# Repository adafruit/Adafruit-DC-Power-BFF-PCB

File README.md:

## Adafruit DC Power BFF Add-On for QT Py PCB

<a href="http://www.adafruit.com/products/5882"><br/>
Click here to purchase one from the Adafruit shop</a>

PCB files for the Adafruit DC Power BFF Add-On for QT Py. 

Format is EagleCAD schematic and board layout
* https://www.adafruit.com/product/5882

### Description

We were recently working on a project where we really wanted to power a QT Py ESP32 from 12V - but the only power input on the board is basically USB 5V max. Never one to give up, we designed an add-on that will allow anyone to use a QT Py or Xiao dev board with up to 20V DC power!

In the center is an MPM3610 integrated buck converter, which will generate 5V from up to 20V input, with cool DC/DC technology so there's no heat-sink needed. The MPM3610 can give about 1 Amp output, which should be plenty even if you have LEDs, WiFi connectivity, displays or even a small motor or servo.

The board features both 3.5mm terminal block and 2.1mm DC jack inputs, protected with a Schottky diode. You can use either to power the board, but don't plug in different power inputs to both - they're wired directly together on the BFF. If you're using the DC jack to power, you can use the terminal block as an 'pass through output' to connect other high-voltage devices.

There's two small enable and an ground solderable pads next to the terminal block so you can use an external switch to disable the converter. 

Since its a bulky add-on with through hole components, compared to most of our other BFF boards, we think it's best to use socket header to plug a QT Py on top, rather than trying to have it solder back-to-back. For that reason we include two 7-pin socket headers. Solder them so that the QT Py sits on the top, there's two break-apart railings that can be used to bolt the board since plugging in a jack requires  mechanical stabilization.

### License

Adafruit invests time and resources providing this open source design, please support Adafruit and open-source hardware by purchasing products from [Adafruit](https://www.adafruit.com)!

Designed by Limor Fried/Ladyada for Adafruit Industries.

Creative Commons Attribution/Share-Alike, all text above must be included in any redistribution. 
See license.txt for additional details.

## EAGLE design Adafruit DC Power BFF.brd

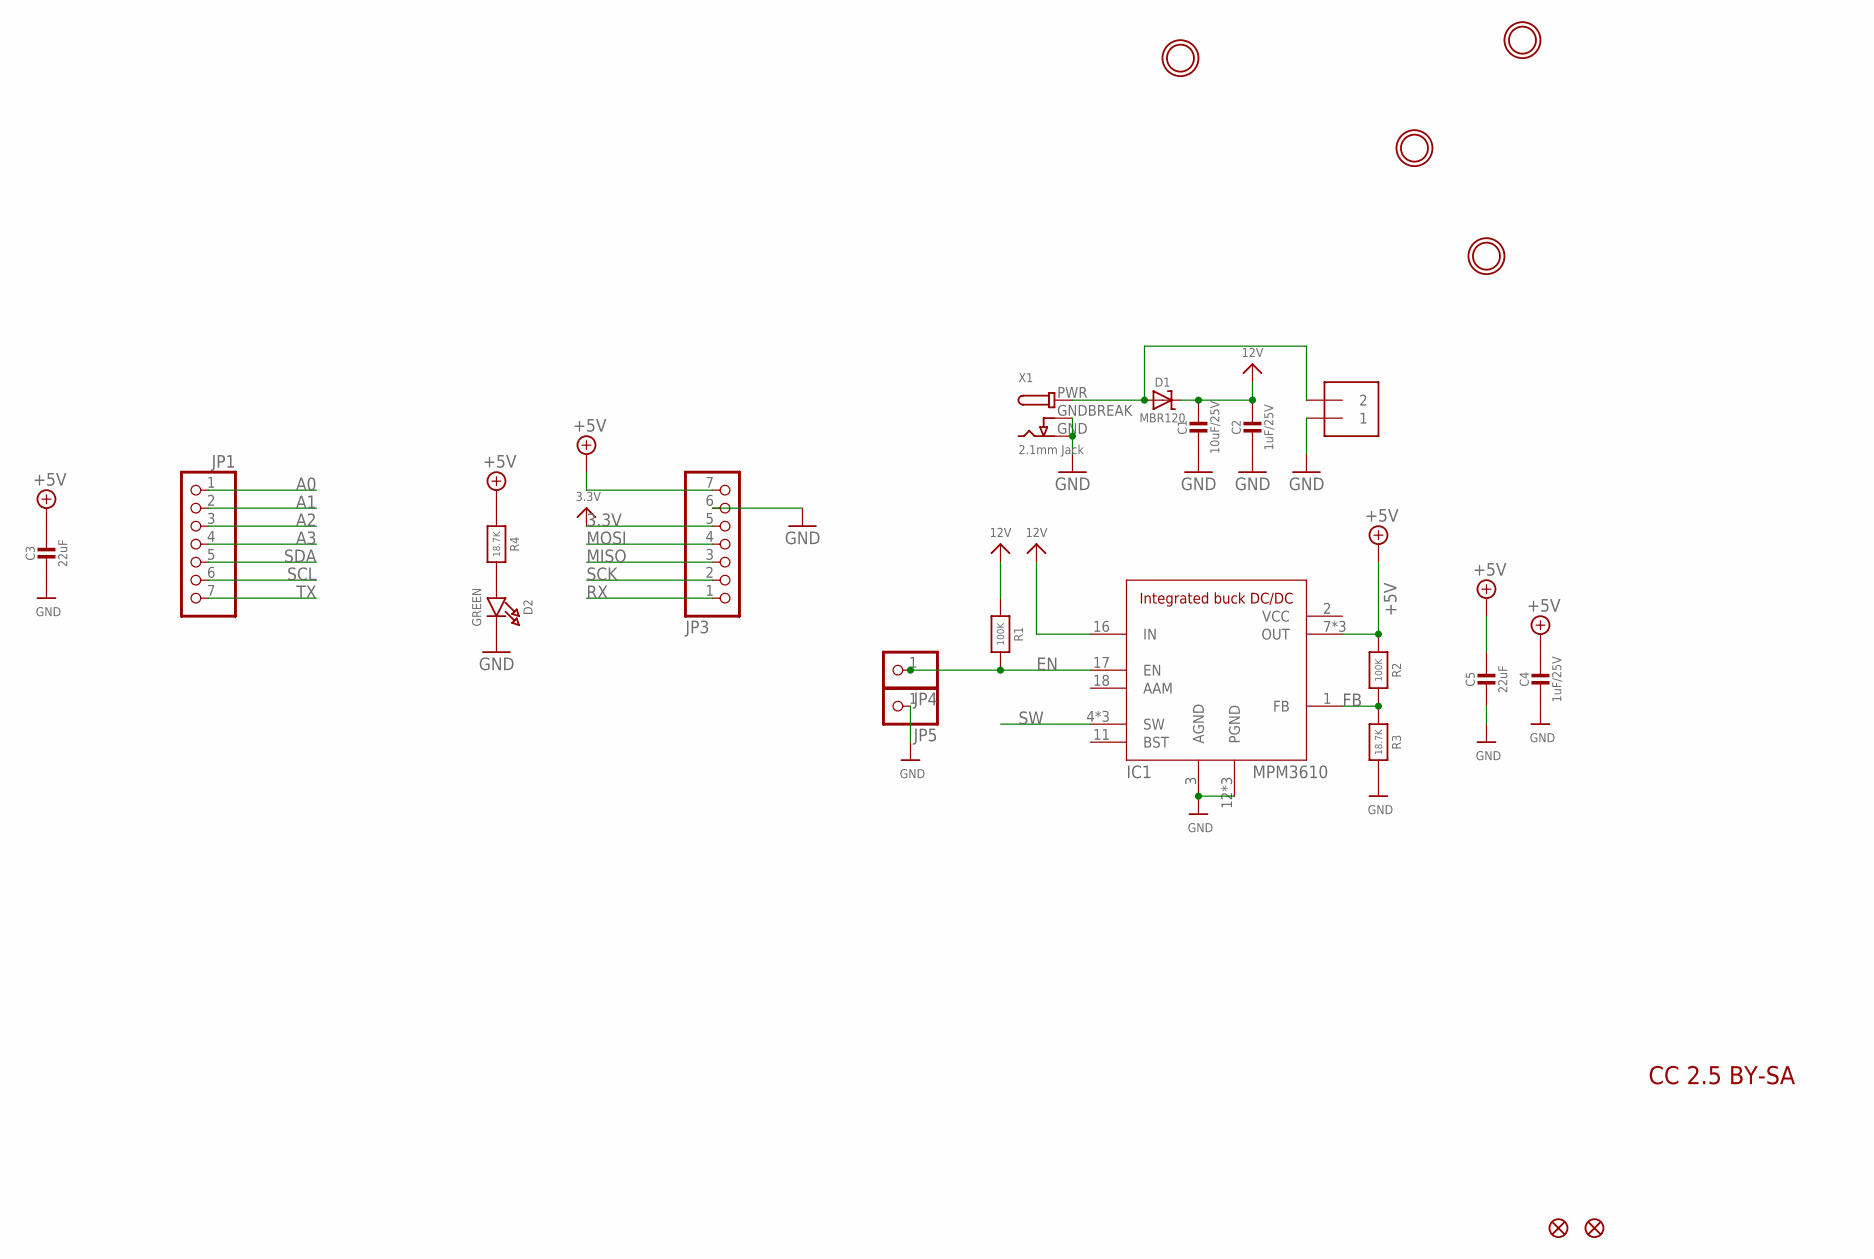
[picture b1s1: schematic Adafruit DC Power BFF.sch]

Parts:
C1: 10uF/25V; 0805-NO
C2, C4: 1uF/25V; 0603-NO
C3, C5: 22uF; 0805-NO
D1: MBR120; SOD-123FL
D2: GREEN; CHIPLED_0603_NOOUTLINE
IC1: MPM3610
J1: 1X2-3.5MM
JP1, JP3: HEADER-1X7THICKER; 1X07_ROUND_76
JP4, JP5: HEADER-1X12MM; 1X01_2MM
R1, R2: 100K; _0402NO
R3, R4: 18.7K; _0402NO
U$6, U$8: FIDUCIAL_1MM
U$14, U$15, U$17, U$18: MOUNTINGHOLE2.5; MOUNTINGHOLE_2.5_PLATED
X1: 2.1mm Jack; DCJACK_2MM_PTH

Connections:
3.3V: JP3.5
12V: C1.1, C2.1, D1.C, IC1.16 (IN), R1.1
+5V: C3.1, C4.1, C5.1, IC1.7 (OUT), IC1.8 (OUT), IC1.9 (OUT), JP3.7, R2.1, R4.1
A0: JP1.1
A1: JP1.2
A2: JP1.3
A3: JP1.4
EN: IC1.17 (EN), JP4.1, R1.2
FB: IC1.1 (FB), R2.2, R3.1
GND: C1.2, C2.2, C3.2, C4.2, C5.2, D2.C, IC1.3 (AGND), IC1.12 (PGND), IC1.13 (PGND), IC1.14 (PGND), J1.1, JP3.6, JP5.1, R3.2, X1.GND, X1.GNDBREAK
MISO: JP3.3
MOSI: JP3.4
unnamed: D2.A, R4.2
unnamed: D1.A, J1.2, X1.PWR
RX: JP3.1
SCK: JP3.2
SCL: JP1.6
SDA: JP1.5
SW: IC1.4 (SW), IC1.5 (SW), IC1.6 (SW)
TX: JP1.7
VCC: IC1.2 (VCC)

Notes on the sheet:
CC 2.5 BY-SA

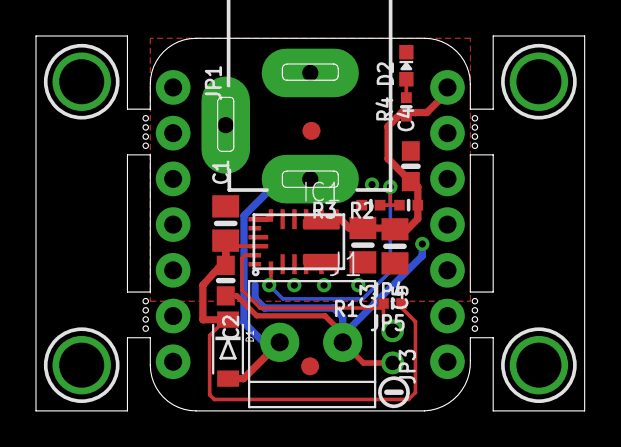
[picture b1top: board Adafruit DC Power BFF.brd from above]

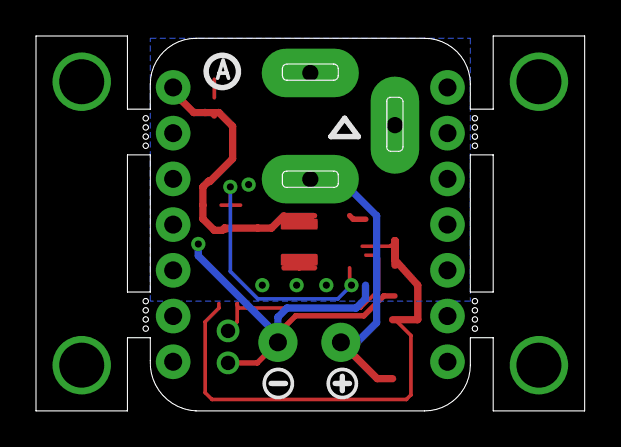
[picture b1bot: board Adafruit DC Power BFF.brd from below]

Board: 2 copper layers, 30.5 x 20.8 mm, 42 parts (5 on the bottom side), 8 nets.

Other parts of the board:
PLABEL1: PLABEL1
PLABEL2: PLABEL2
PLABEL3: PLABEL3
PLABEL5: PLABEL5
PLABEL6: PLABEL6
PLABEL7: PLABEL7
PLABEL8: PLABEL8
PLABEL11: PLABEL11
PLABEL12: PLABEL12
PLABEL13: PLABEL13
PLABEL14: PLABEL14
PLABEL19: PLABEL19
PLABEL20: PLABEL20
PLABEL21: PLABEL21
U$3: PCBFEAT-REV-040
U$12, U$20: SYMBOL_MINUS
U$19: SYMBOL_PLUS

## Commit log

2024-02-09 cookiecutter

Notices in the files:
parts and their libraries:
microbuilder: This work is placed in the public domain, and may be freely used for commercial and non-commercial work with the following conditions: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
